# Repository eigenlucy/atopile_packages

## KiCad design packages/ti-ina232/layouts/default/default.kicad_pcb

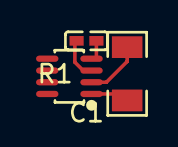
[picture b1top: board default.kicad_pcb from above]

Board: 2 copper layers, 3 parts (0 on the bottom side), 4 nets.

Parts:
C1: 100nF ±10% 16V X7R; C0402
R1: 0Ω 250mW; R1206
U1: SOT-23-8_L2.9-W1.6-P0.65-LS2.8-BR

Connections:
IN_: R1.2, U1.2
INplus: R1.1, U1.1
gnd: C1.2, U1.3
hv: C1.1, U1.4

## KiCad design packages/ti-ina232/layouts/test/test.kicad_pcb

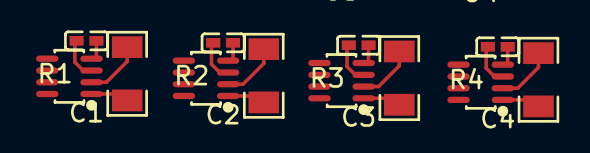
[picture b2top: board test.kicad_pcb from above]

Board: 2 copper layers, 12 parts (0 on the bottom side), 12 nets.

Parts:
C1, C2, C3, C4: 100nF ±10% 16V X7R; C0402
R1: 800mΩ ±1% 250mW; R1206
R2: 70mΩ ±1% 500mW; R1206
R3: 25mΩ ±1% 1W; R1206
R4: 7mΩ ±1% 1W; R1206
U1, U2, U3, U4: SOT-23-8_L2.9-W1.6-P0.65-LS2.8-BR

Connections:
IN_: R1.2, U1.2
INplus: R1.1, U1.1
SCL: U1.5, U2.5, U3.5, U4.5, U4.7
SDA: U1.6, U2.6, U3.6, U3.7, U4.6
current_sensors[2]-IN_: R3.2, U3.2
current_sensors[2]-INplus: R3.1, U3.1
current_sensors[3]-IN_: R4.2, U4.2
current_sensors[3]-INplus: R4.1, U4.1
gnd: R2.1, U2.1
gnd-1: R2.2, U2.2
gnd-2: C1.2, C2.2, C3.2, C4.2, U1.3, U1.7, U2.3, U3.3, U4.3
hv: C1.1, C2.1, C3.1, C4.1, U1.4, U2.4, U2.7, U3.4, U4.4

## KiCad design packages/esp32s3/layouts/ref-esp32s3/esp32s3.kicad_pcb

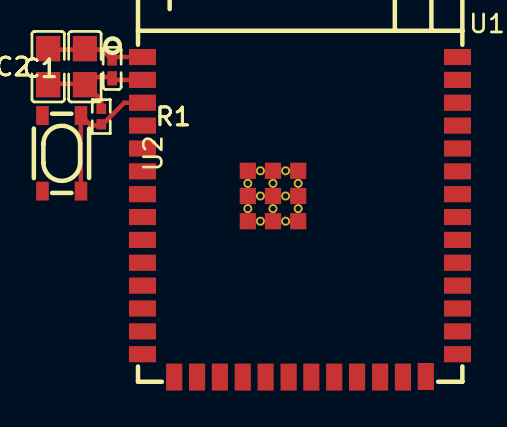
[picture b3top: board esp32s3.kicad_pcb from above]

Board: 2 copper layers, 6 parts (0 on the bottom side), 3 nets.

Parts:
C1: 100nF ±10% 16V X7R; C0402-b3ef17
C2, C3: 10µF ±10% 25V X5R; C0805-3b2e55
R1: 10kΩ ±1% 62.5mW; R0402-56259e
U1: WIRELM-SMD_ESP32-S3-WROOM-1
U2: KEY-SMD_4P-L4.2-W3.2-P2.20-LS4.6

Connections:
gnd: C1.2, C2.2, C3.2, U1.1, U1.40, U1.41, U2.3, U2.4
hv: C1.1, C2.1, C3.1, R1.1, U1.2
input: R1.2, U2.1, U2.2

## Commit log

2025-05-20 test
2025-05-20 test 2
2025-05-20 added .python-version
2025-05-20 added precommit config
2025-05-20 fixed button description
2025-05-20 added e22900m22s listing
2025-05-20 updated esp32s3 id
2025-05-26 added dw01
2025-05-26 fixed
2025-06-17 forked ina232
2025-06-18 fixed?
